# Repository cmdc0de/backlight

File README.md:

# backlight
ultimately will be fractal art back lit by a set of APA107

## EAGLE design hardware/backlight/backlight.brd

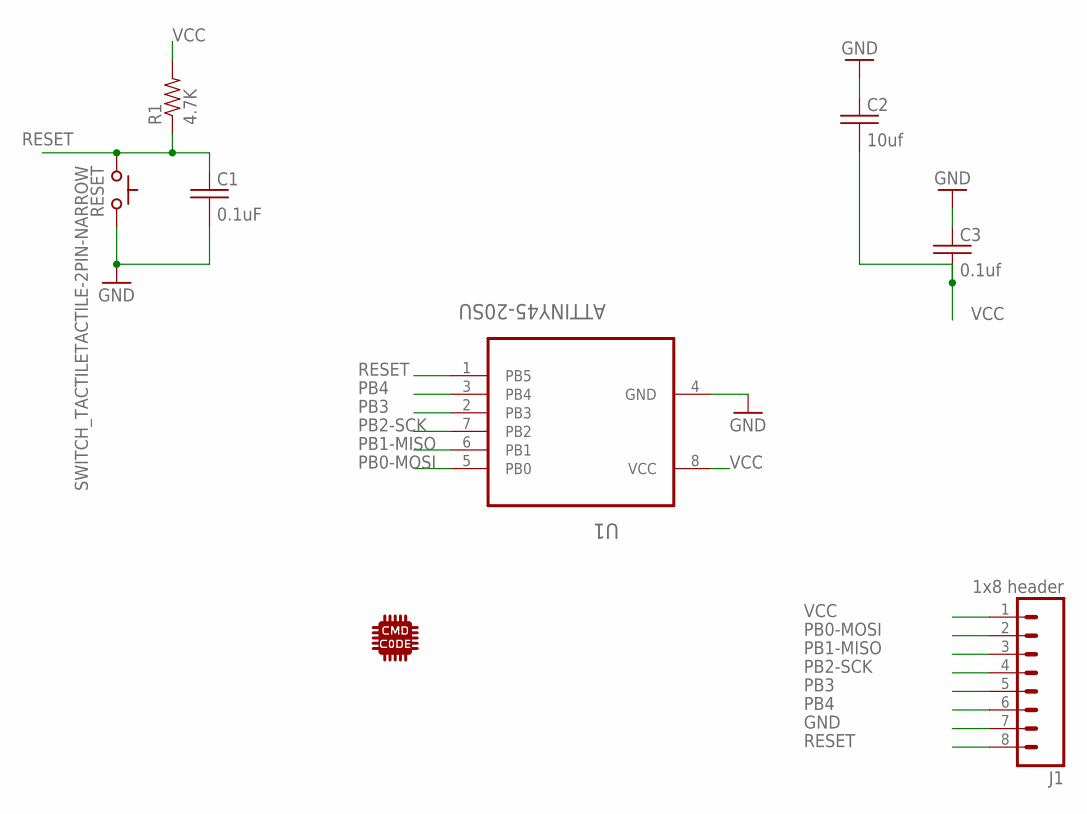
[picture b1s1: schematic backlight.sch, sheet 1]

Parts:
C1: 0.1uF; C0805K
C2: 10uf; C0805K
C3: 0.1uf; C0805K
J1: 1x8 header; 1X08
R1: 4.7K; R0805
RESET: SWITCH_TACTILETACTILE-2PIN-NARROW; TACTILE-2PIN-NARROW
U1: ATTINY45-20SU; SOIC127P798X216-8N
U$17: CMD_C0DE_LOGOCMD_CODE_LOGO_TOP_COPPER; CMD_C0DE_LOGO_TOP_COPPER

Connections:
GND: C1.2, C2.1, C3.1, J1.7, RESET.P$1 (A), U1.4 (GND); also elsewhere on the board
PB0-MOSI: J1.2, U1.5 (PB0); also elsewhere on the board
PB1-MISO: J1.3, U1.6 (PB1)
PB2-SCK: J1.4, U1.7 (PB2); also elsewhere on the board
PB3: J1.5, U1.2 (PB3)
PB4: J1.6, U1.3 (PB4)
RESET: C1.1, J1.8, R1.1, RESET.P$2 (C), U1.1 (PB5)
VCC: C2.2, C3.2, J1.1, R1.2, U1.8 (VCC); also elsewhere on the board

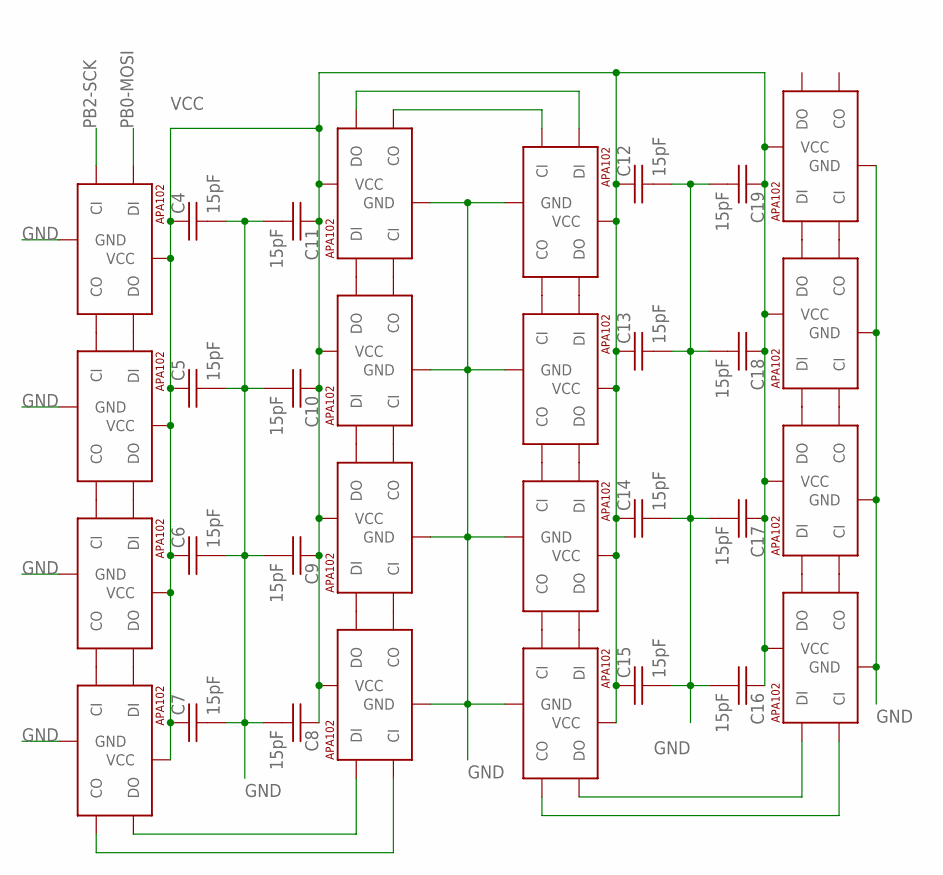
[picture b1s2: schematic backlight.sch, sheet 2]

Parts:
C4, C5, C6, C7, C8, C9, C10, C11, C12, C13, C14, C15, C16, C17, C18, C19: 15pF; C0805K
U$1, U$2, U$3, U$4, U$5, U$6, U$7, U$8, U$9, U$10, U$11, U$12, U$13, U$14, U$15, U$16: APA1025050; APA102_5050

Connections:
GND: C4.2, C5.2, C6.2, C7.2, C8.2, C9.2, C10.2, C11.2, C12.2, C13.2, C14.2, C15.2, C16.2, C17.2, C18.2, C19.2, U$1.6 (GND), U$2.6 (GND), U$3.6 (GND), U$4.6 (GND), U$5.6 (GND), U$6.6 (GND), U$7.6 (GND), U$8.6 (GND), U$9.6 (GND), U$10.6 (GND), U$11.6 (GND), U$12.6 (GND), U$13.6 (GND), U$14.6 (GND), U$15.6 (GND), U$16.6 (GND); also elsewhere on the board
unnamed: U$8.2 (CO), U$9.5 (CI)
unnamed: U$8.3 (DO), U$9.4 (DI)
unnamed: U$1.2 (CO), U$2.5 (CI)
unnamed: U$1.3 (DO), U$2.4 (DI)
unnamed: U$3.2 (CO), U$4.5 (CI)
unnamed: U$3.3 (DO), U$4.4 (DI)
unnamed: U$2.2 (CO), U$3.5 (CI)
unnamed: U$2.3 (DO), U$3.4 (DI)
unnamed: U$5.2 (CO), U$6.5 (CI)
unnamed: U$5.3 (DO), U$6.4 (DI)
unnamed: U$7.2 (CO), U$8.5 (CI)
unnamed: U$7.3 (DO), U$8.4 (DI)
unnamed: U$6.2 (CO), U$7.5 (CI)
unnamed: U$6.3 (DO), U$7.4 (DI)
unnamed: U$12.3 (DO), U$13.4 (DI)
unnamed: U$9.2 (CO), U$10.5 (CI)
unnamed: U$9.3 (DO), U$10.4 (DI)
unnamed: U$12.2 (CO), U$13.5 (CI)
unnamed: U$11.2 (CO), U$12.5 (CI)
unnamed: U$11.3 (DO), U$12.4 (DI)
unnamed: U$10.2 (CO), U$11.5 (CI)
unnamed: U$10.3 (DO), U$11.4 (DI)
unnamed: U$13.2 (CO), U$14.5 (CI)
unnamed: U$13.3 (DO), U$14.4 (DI)
unnamed: U$15.2 (CO), U$16.5 (CI)
unnamed: U$15.3 (DO), U$16.4 (DI)
unnamed: U$14.2 (CO), U$15.5 (CI)
unnamed: U$14.3 (DO), U$15.4 (DI)
unnamed: U$4.3 (DO), U$5.4 (DI)
unnamed: U$4.2 (CO), U$5.5 (CI)
PB0-MOSI: U$1.4 (DI); also elsewhere on the board
PB2-SCK: U$1.5 (CI); also elsewhere on the board
VCC: C4.1, C5.1, C6.1, C7.1, C8.1, C9.1, C10.1, C11.1, C12.1, C13.1, C14.1, C15.1, C16.1, C17.1, C18.1, C19.1, U$1.1 (VCC), U$2.1 (VCC), U$3.1 (VCC), U$4.1 (VCC), U$5.1 (VCC), U$6.1 (VCC), U$7.1 (VCC), U$8.1 (VCC), U$9.1 (VCC), U$10.1 (VCC), U$11.1 (VCC), U$12.1 (VCC), U$13.1 (VCC), U$14.1 (VCC), U$15.1 (VCC), U$16.1 (VCC); also elsewhere on the board

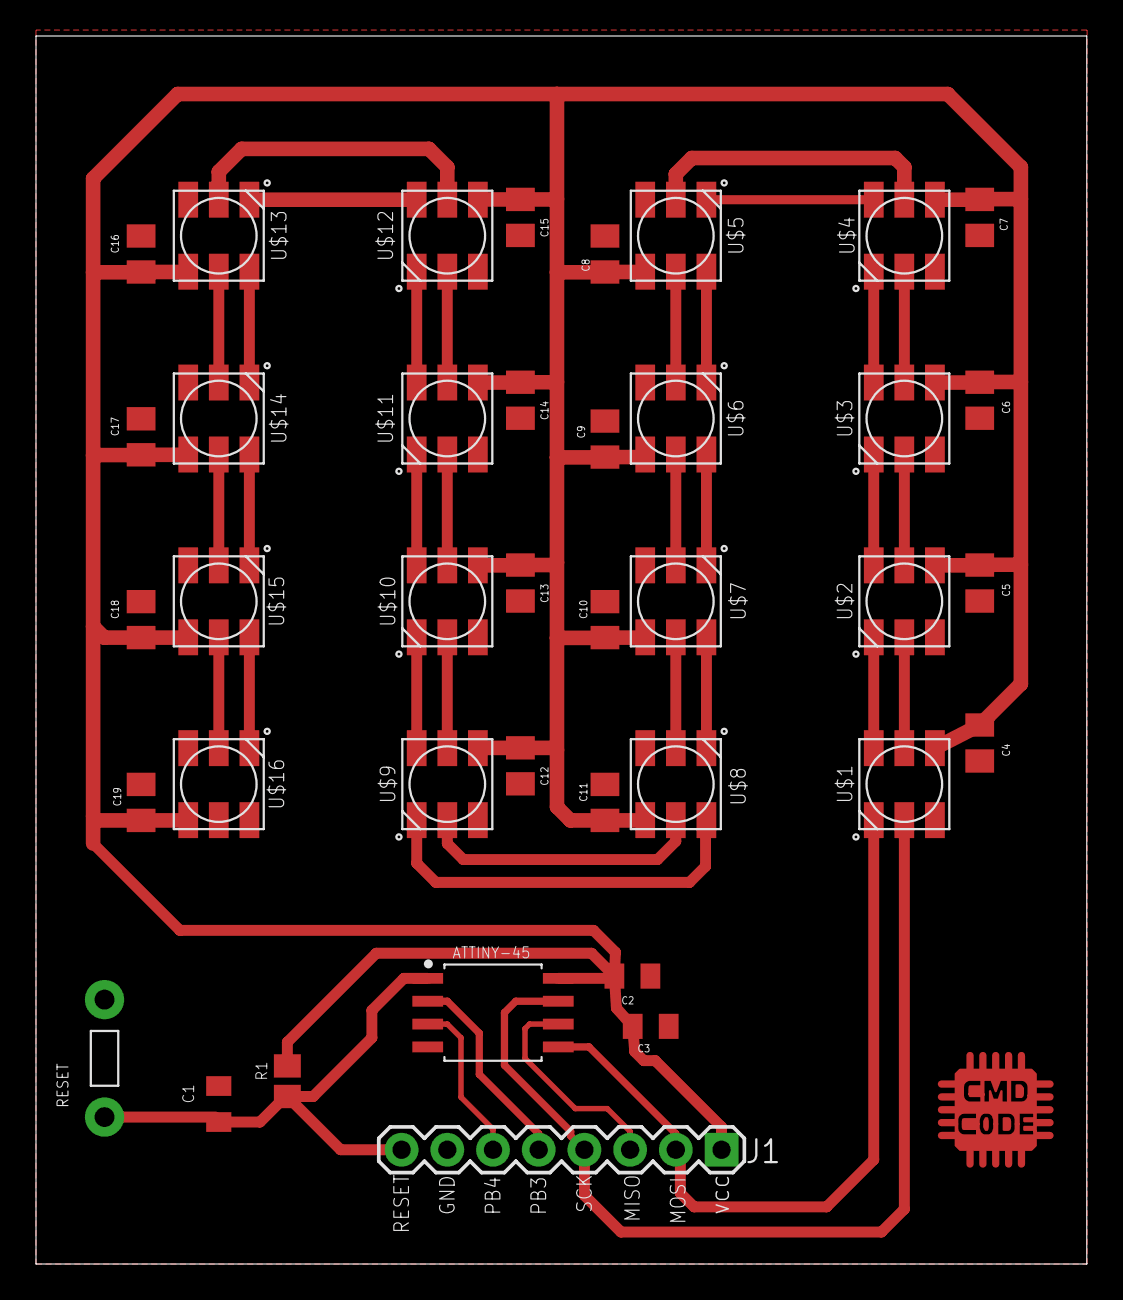
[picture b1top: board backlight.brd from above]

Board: 2 copper layers, 58.4 x 68.2 mm, 40 parts (0 on the bottom side), 38 nets.

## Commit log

2019-11-24 initial checkin
2019-11-24 adding gitignore
2019-11-29 thicked traces and started real board
2019-11-30 thicken traces again
